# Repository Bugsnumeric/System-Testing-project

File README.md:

Diagrama proiectului:

Componente folosite impreuna cu detalii despre acestea:

| Component | Part Number | Package | Function | Datasheet |
|-----------|------------|---------|----------|-----------|
| MCU | nRF52840-QIAA-R | aQFN73 (7x7) | Microcontroller + BLE + USB | [Datasheet](https://docs.nordicsemi.com/) |
| Charger / Power Path | BQ25180YBGR | DSBGA-8 | Li-Ion/LiPo charger with power path | [Datasheet](https://www.ti.com/lit/ds/symlink/bq25180.pdf) |
| Buck-Boost Regulator | RT6160AWSC | WLCSP-15 | 3.3V system rail regulator | [Datasheet](https://www.richtek.com/assets/product_file/RT6160A/DS6160A-05.pdf) |
| Fuel Gauge | MAX17048G+T10 | DFN-8 (2x2) | Battery SOC monitoring | [Datasheet](https://www.analog.com/media/en/technical-documentation/data-sheets/MAX17048-MAX17049.pdf) |
| Accelerometer | BMA421 | LGA-12 (2x2) | Step counting + motion wake | [Datasheet](https://jlcpcb.com/partdetail/Bosch_Sensortec-BMA421/C5242966) |
| Haptic Driver | DRV2605LDGSR | VSSOP-10 | ERM motor driver with effects library | [Datasheet](https://www.ti.com/lit/ds/symlink/drv2605l.pdf) |
| PFET (EPD power) | SI2301CDS | SOT-23 | E-paper display power gating | [Datasheet](https://jlcpcb.com/partdetail/Changjiang_Electronics_Tech_CJ-SI2301CDS/C10487) |
| USB ESD Protection | USBLC6-2SC6Y | SOT-23-6 | ESD protection on USB data lines | [Datasheet](https://www.st.com/resource/en/datasheet/usblc6-2.pdf) |
| USB Type-C Connector | KH-TYPE-C-16P | 16-pin SMD | USB charging + data | [Datasheet](#) |

Descriere funcționalitate hardware

Interfețe:

I2C: încărcător LiPo, regulator DC/DC, IMU, fuel gauge, driver haptic
SPI: display e-paper

Sheet 1:

Încărcătorul LiPo gestionează încărcarea bateriei
Regulatorul DC/DC asigură o tensiune stabilă de 3.3V pentru sistem
IMU (accelerometru) măsoară accelerația pe 3 axe și permite funcții precum numărarea pașilor
Microcontrollerul nRF52840 coordonează toate funcțiile plăcii
Interfața SWD este utilizată pentru programare și debug

Sheet 2:

Circuitul de comandă pentru e-paper alimentează și controlează display-ul
Conectorul e-paper realizează legătura fizică cu display-ul
Fuel gauge monitorizează nivelul de încărcare al bateriei
Conectorul USB-C permite alimentarea și transferul de date
Protecția ESD previne deteriorarea cauzată de descărcări electrostatice
Driverul haptic controlează motorul de vibrație
Butoanele oferă interfața de control pentru utilizator

## Descriere pini nRF52840  

| Pin | Descriere |
|-----|----------|
| VDD | Alimentare 3V3 |
| DCC | Power regulation |
| DEC4 | Power regulation |
| VSS | GND |
| P0.31 / AIN7-4 | Nefolosit |
| P0.02 / AIN0 | SPI SCK (clock pentru display) |
| P0.02 / AIN0 | SPI MOSI (master output slave in) |
| P1.15–P1.12 | Nefolosit |
| DEC2 | GND, power regulation |
| P1.12–P1.11 | Nefolosit |
| VDD | Alimentare 3V3 |
| XC2, XC1 | Oscilator X1 (32 MHz) |
| DEC3 | GND |
| DEC6 | Power regulation |
| VSS_PA | Alimentare antenă |
| ANT | Conectare antenă |
| P0.10 / NFC2 | Semnal alertă baterie (Fuel Gauge) |
| P0.09 / NFC1 | Nefolosit |
| DEC5 | GND, power regulation |
| P1.07–P1.03 | Nefolosit |
| P1.02 | Buton Down |
| P1.01 | Control alimentare display |
| SWDIO, SWDCLK | Programare și debug |
| VDD | Alimentare 3V3 |
| VSS_PAD | GND |
| P1.00 | SWO (debug) |
| P0.25–P0.19 | Nefolosit |
| P0.18 / RESET | Pin Reset |
| P0.17, P0.16, P0.15 | Interfață display |
| P0.13, P0.14 | Butoane Enter / Up |
| D-, D+ | USB (transmisie diferențială) |
| VBUS | Alimentare USB 5V |
| DEC3V3 | GND (intern, power regulation) |
| DCCH | Nefolosit |
| VDDH, VDD | Alimentare 3V3 |
| P0.12 | Enable driver haptic |
| P0.11 | Alertă alimentare (de la LiPo Charger) |
| P1.09 | Nefolosit |
| P1.08, P0.08 | Interrupții IMU |
| P0.07, P0.06 | I2C (SCL, SDA) |
| P0.05 / AIN3 | Chip Select display |
| P0.04 / AIN2, P0.27, P0.26 | Nefolosit |
| XL2, XL1 | Oscilator X2 (32 kHz) |
| DEC1 | GND, power regulation |

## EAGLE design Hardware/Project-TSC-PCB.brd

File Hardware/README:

Print-out schematic:

https://a360.co/4sF2GDH

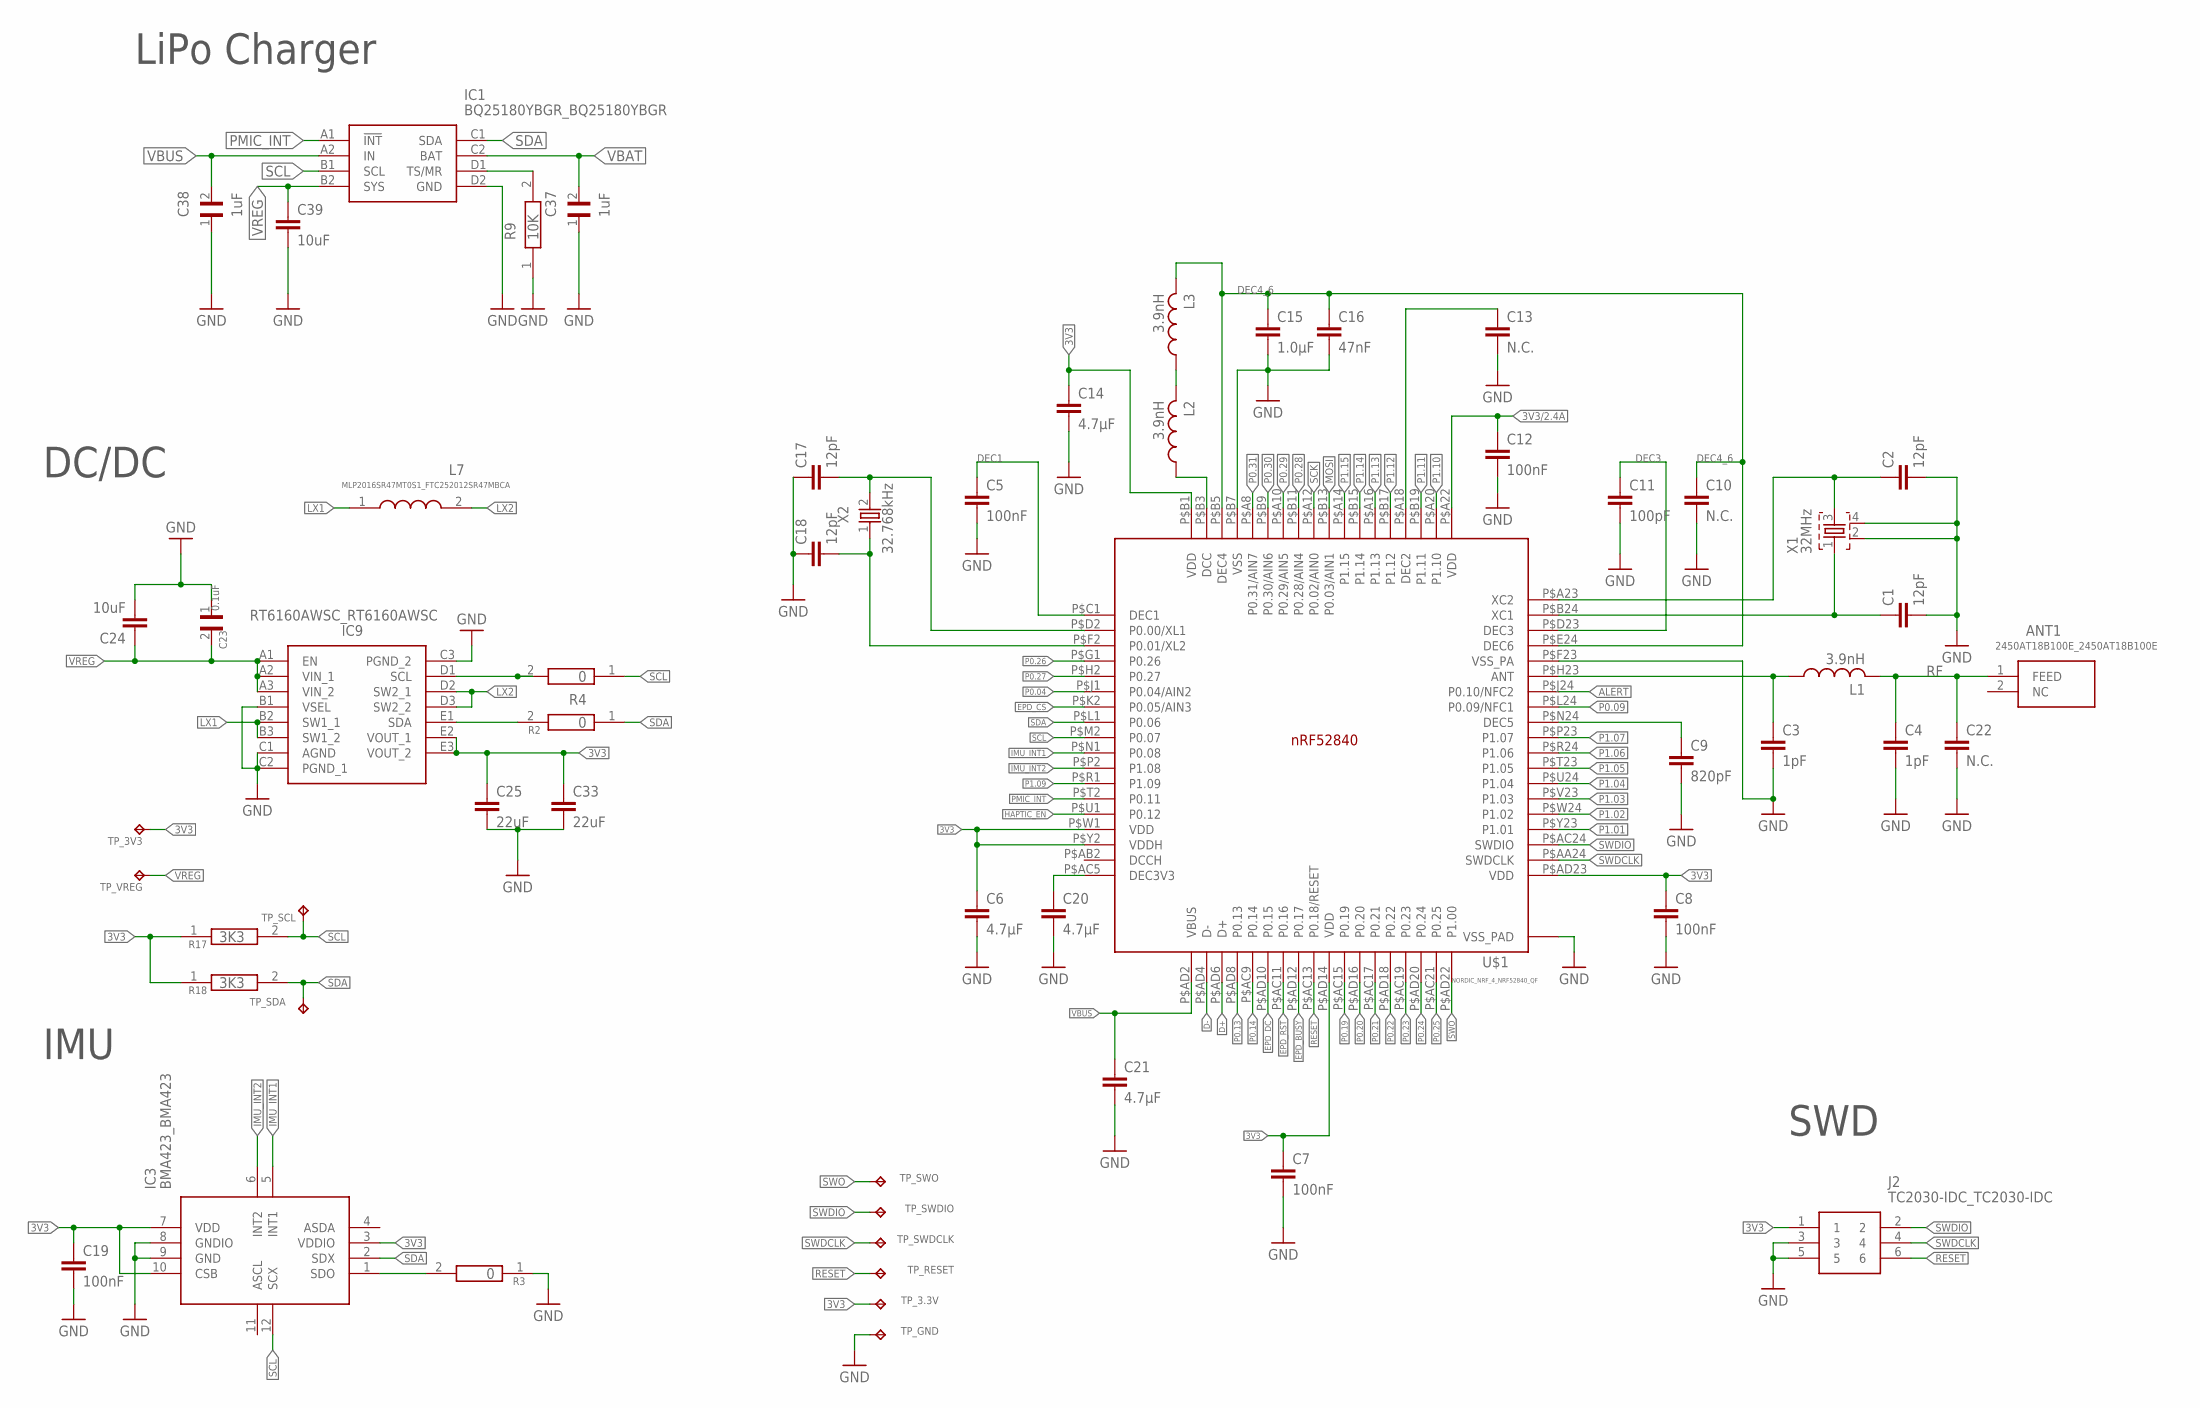
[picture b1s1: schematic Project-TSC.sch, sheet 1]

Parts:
ANT1: 2450AT18B100E_2450AT18B100E; 2450AT18B100E_ANTC3216X140N
C1, C2, C17, C18: 12pF; NORDIC_NRF_3_RESC0201_L
C3, C4: 1pF; NORDIC_NRF_3_RESC0201_L
C5, C7, C8, C12: 100nF; NORDIC_NRF_3_RESC0201_L
C6, C14, C20, C21: 4.7µF; PERFECT_0402_0402
C9: 820pF; NORDIC_NRF_3_RESC0201_L
C10, C13, C22: N.C.; NORDIC_NRF_3_RESC0201_L
C11: 100pF; NORDIC_NRF_3_RESC0201_L
C15: 1.0µF; PERFECT_0402_0402
C16: 47nF; NORDIC_NRF_3_RESC0201_L
C19: 100nF; PERFECT_0402_0402
C23: 0.1uF; GRM011R60J152KE01L_1_0201
C24, C39: 10uF; PERFECT_0402_0402
C25, C33: 22uF; PERFECT_0402_0402
C37, C38: 1uF; GRM011R60J152KE01L_1_0201
IC1: BQ25180YBGR_BQ25180YBGR; BQ25180YBGR_BGA8C40P2X4_100X155X50
IC3: BMA423_BMA423
IC9: RT6160AWSC_RT6160AWSC; RT6160AWSC_BGA15C40P3X5_140X230X60
J2: TC2030-IDC_TC2030-IDC; TC2030-IDC_TC2030IDC
L1, L2, L3: 3.9nH; NORDIC_NRF_2_RESC0402_L
L7: MLP2016SR47MT0S1_FTC252012SR47MBCA; MLP2016SR47MT0S1_INDC2016X100N
R2, R3, R4: 0; CPF0201D7K68C1_0201
R9: 10K; CPF0201D7K68C1_0201
R17, R18: 3K3; CPF0201D7K68C1_0201
TP_3.3V, TP_3V3: HECTOR_WATCH_1_TPTP20R; HECTOR_WATCH_1_TP20R
TP_GND: HECTOR_WATCH_1_TPTP20R; HECTOR_WATCH_1_TP20R
TP_RESET: HECTOR_WATCH_1_TPTP20R; HECTOR_WATCH_1_TP20R
TP_SCL: HECTOR_WATCH_1_TPTP20R; HECTOR_WATCH_1_TP20R
TP_SDA: HECTOR_WATCH_1_TPTP20R; HECTOR_WATCH_1_TP20R
TP_SWDCLK: HECTOR_WATCH_1_TPTP20R; HECTOR_WATCH_1_TP20R
TP_SWDIO: HECTOR_WATCH_1_TPTP20R; HECTOR_WATCH_1_TP20R
TP_SWO: HECTOR_WATCH_1_TPTP20R; HECTOR_WATCH_1_TP20R
TP_VREG: HECTOR_WATCH_1_TPTP20R; HECTOR_WATCH_1_TP20R
U$1: NORDIC_NRF_4_NRF52840_QF; NORDIC_NRF_4_AQFN50P700X700X85_HS-74N
X1: 32MHz; NORDIC_NRF_BT-XTAL_2016_N
X2: 32.768kHz; NORDIC_NRF_1_XTAL_3215_N

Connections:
3V3: C6.1, C7.1, C8.1, C14.1, C19.1, C25.1, C33.1, IC3.3 (VDDIO), IC3.7 (VDD), IC3.10 (CSB), IC9.E2 (VOUT_1), IC9.E3 (VOUT_2), J2.1, R17.1, R18.1, TP_3.3V.TP, TP_3V3.TP, U$1.P$AD14 (VDD), U$1.P$AD23 (VDD), U$1.P$B1 (VDD), U$1.P$W1 (VDD), U$1.P$Y2 (VDDH); also elsewhere on the board
3V3/2.4A: C12.1, U$1.P$A22 (VDD)
ALERT: U$1.P$J24 (P0.10/NFC2); also elsewhere on the board
D+: U$1.P$AD6 (D+); also elsewhere on the board
D-: U$1.P$AD4 (D-); also elsewhere on the board
DEC1: C5.1, U$1.P$C1 (DEC1)
DEC3: C11.1, U$1.P$D23 (DEC3)
DEC4_6: C10.1, C15.1, C16.1, L3.2, U$1.P$B5 (DEC4), U$1.P$E24 (DEC6)
EPD_BUSY: U$1.P$AD12 (P0.17); also elsewhere on the board
EPD_CS: U$1.P$K2 (P0.05/AIN3); also elsewhere on the board
EPD_DC: U$1.P$AD10 (P0.15); also elsewhere on the board
EPD_RST: U$1.P$AC11 (P0.16); also elsewhere on the board
GND: C1.2, C2.2, C3.2, C4.2, C5.2, C6.2, C7.2, C8.2, C9.2, C10.2, C11.2, C12.2, C13.2, C14.2, C15.2, C16.2, C17.1, C18.1, C19.2, C20.2, C21.2, C22.2, C23.1, C24.2, C25.2, C33.2, C37.1, C38.1, C39.2, IC1.D2 (GND), IC3.8 (GNDIO), IC3.9 (GND), IC9.B1 (VSEL), IC9.C1 (AGND), IC9.C2 (PGND_1), IC9.C3 (PGND_2), J2.3, J2.5, R3.1, R9.1, TP_GND.TP, U$1.P$74 (VSS_PAD), U$1.P$75 (VSS_PAD), U$1.P$76 (VSS_PAD), U$1.P$77 (VSS_PAD), U$1.P$78 (VSS_PAD), U$1.P$79 (VSS_PAD), U$1.P$80 (VSS_PAD), U$1.P$81 (VSS_PAD), U$1.P$82 (VSS_PAD), U$1.P$83 (VSS_PAD), U$1.P$84 (VSS_PAD), U$1.P$85 (VSS_PAD), U$1.P$86 (VSS_PAD), U$1.P$87 (VSS_PAD), U$1.P$88 (VSS_PAD), U$1.P$89 (VSS_PAD), U$1.P$90 (VSS_PAD), U$1.P$B7 (VSS), U$1.P$F23 (VSS_PA), X1.2, X1.4; also elsewhere on the board
HAPTIC_EN: U$1.P$U1 (P0.12); also elsewhere on the board
IMU_INT1: IC3.5 (INT1), U$1.P$N1 (P0.08)
IMU_INT2: IC3.6 (INT2), U$1.P$P2 (P1.08)
LX1: IC9.B2 (SW1_1), IC9.B3 (SW1_2), L7.1
LX2: IC9.D2 (SW2_1), IC9.D3 (SW2_2), L7.2
MOSI: U$1.P$B13 (P0.03/AIN1); also elsewhere on the board
unnamed: IC1.D1 (TS/MR), R9.2
unnamed: C9.1, U$1.P$N24 (DEC5)
unnamed: IC9.D1 (SCL), R4.2
unnamed: IC9.E1 (SDA), R2.2
unnamed: IC3.1 (SDO), R3.2
unnamed: C3.1, L1.1, U$1.P$H23 (ANT)
unnamed: C1.1, U$1.P$B24 (XC1), X1.1
unnamed: C2.1, U$1.P$A23 (XC2), X1.3
unnamed: C13.1, U$1.P$A18 (DEC2)
unnamed: L2.2, L3.1
unnamed: L2.1, U$1.P$B3 (DCC)
unnamed: C17.2, U$1.P$D2 (P0.00/XL1), X2.2
unnamed: C18.2, U$1.P$F2 (P0.01/XL2), X2.1
unnamed: C20.1, U$1.P$AC5 (DEC3V3)
P0.04: U$1.P$J1 (P0.04/AIN2)
P0.09: U$1.P$L24 (P0.09/NFC1)
P0.13: U$1.P$AD8 (P0.13); also elsewhere on the board
P0.14: U$1.P$AC9 (P0.14); also elsewhere on the board
P0.19: U$1.P$AC15 (P0.19)
P0.20: U$1.P$AD16 (P0.20)
P0.21: U$1.P$AC17 (P0.21)
P0.22: U$1.P$AD18 (P0.22)
P0.23: U$1.P$AC19 (P0.23)
P0.24: U$1.P$AD20 (P0.24)
P0.25: U$1.P$AC21 (P0.25)
P0.26: U$1.P$G1 (P0.26)
P0.27: U$1.P$H2 (P0.27)
P0.28: U$1.P$B11 (P0.28/AIN4)
P0.29: U$1.P$A10 (P0.29/AIN5)
P0.30: U$1.P$B9 (P0.30/AIN6)
P0.31: U$1.P$A8 (P0.31/AIN7)
P1.01: U$1.P$Y23 (P1.01); also elsewhere on the board
P1.02: U$1.P$W24 (P1.02); also elsewhere on the board
P1.03: U$1.P$V23 (P1.03)
P1.04: U$1.P$U24 (P1.04)
P1.05: U$1.P$T23 (P1.05)
P1.06: U$1.P$R24 (P1.06)
P1.07: U$1.P$P23 (P1.07)
P1.09: U$1.P$R1 (P1.09)
P1.10: U$1.P$A20 (P1.10)
P1.11: U$1.P$B19 (P1.11)
P1.12: U$1.P$B17 (P1.12)
P1.13: U$1.P$A16 (P1.13)
P1.14: U$1.P$B15 (P1.14)
P1.15: U$1.P$A14 (P1.15)
PMIC_INT: IC1.A1 (!INT), U$1.P$T2 (P0.11)
RESET: J2.6, TP_RESET.TP, U$1.P$AC13 (P0.18/RESET)
RF: ANT1.1 (FEED), C4.1, C22.1, L1.2
SCK: U$1.P$A12 (P0.02/AIN0); also elsewhere on the board
SCL: IC1.B1 (SCL), IC3.12 (SCX), R4.1, R17.2, TP_SCL.TP, U$1.P$M2 (P0.07); also elsewhere on the board
SDA: IC1.C1 (SDA), IC3.2 (SDX), R2.1, R18.2, TP_SDA.TP, U$1.P$L1 (P0.06); also elsewhere on the board
SWDCLK: J2.4, TP_SWDCLK.TP, U$1.P$AA24 (SWDCLK)
SWDIO: J2.2, TP_SWDIO.TP, U$1.P$AC24 (SWDIO)
SWO: TP_SWO.TP, U$1.P$AD22 (P1.00)
VBAT: C37.2, IC1.C2 (BAT); also elsewhere on the board
VBUS: C21.1, C38.2, IC1.A2 (IN), U$1.P$AD2 (VBUS); also elsewhere on the board
VREG: C23.2, C24.1, C39.1, IC1.B2 (SYS), IC9.A1 (EN), IC9.A2 (VIN_1), IC9.A3 (VIN_2), TP_VREG.TP

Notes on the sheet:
LiPo Charger
DC/DC
IMU
SWD

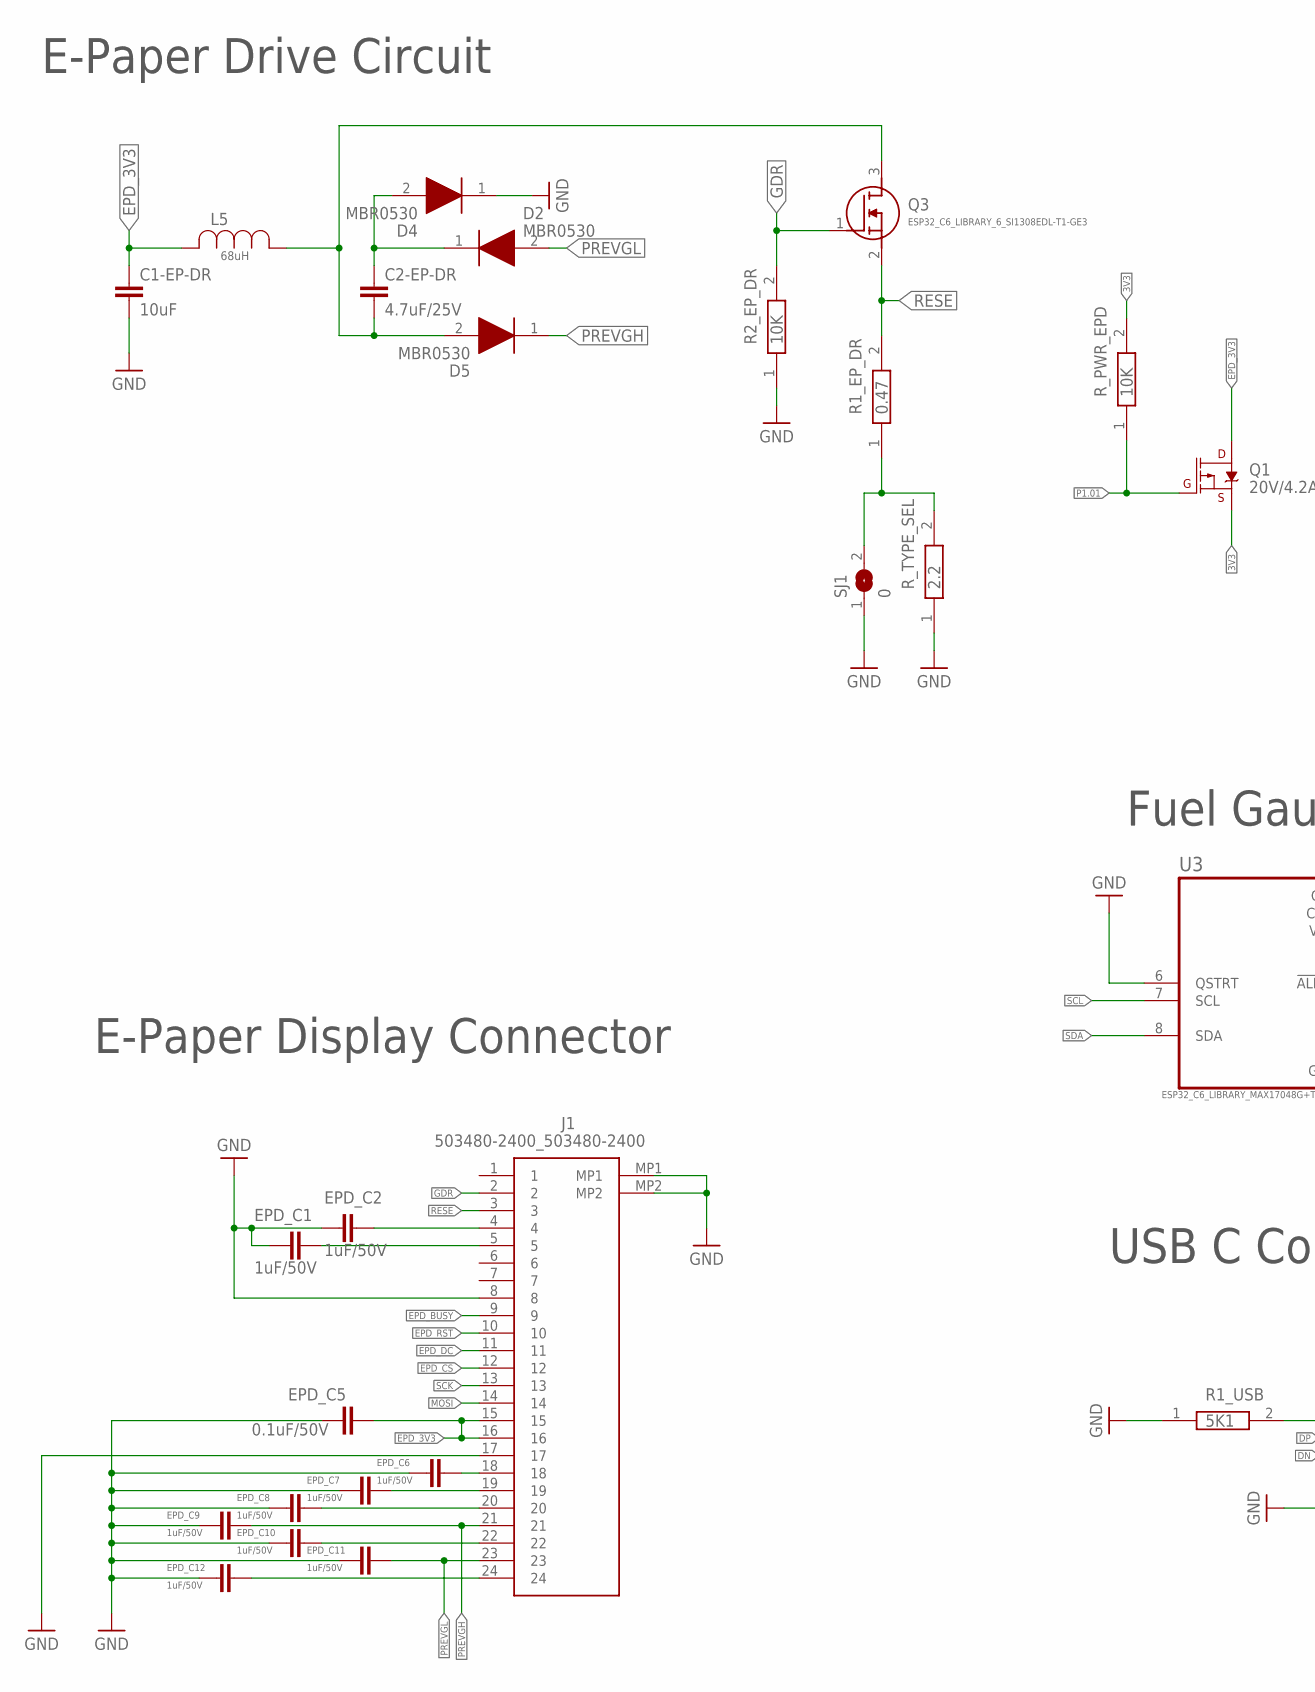
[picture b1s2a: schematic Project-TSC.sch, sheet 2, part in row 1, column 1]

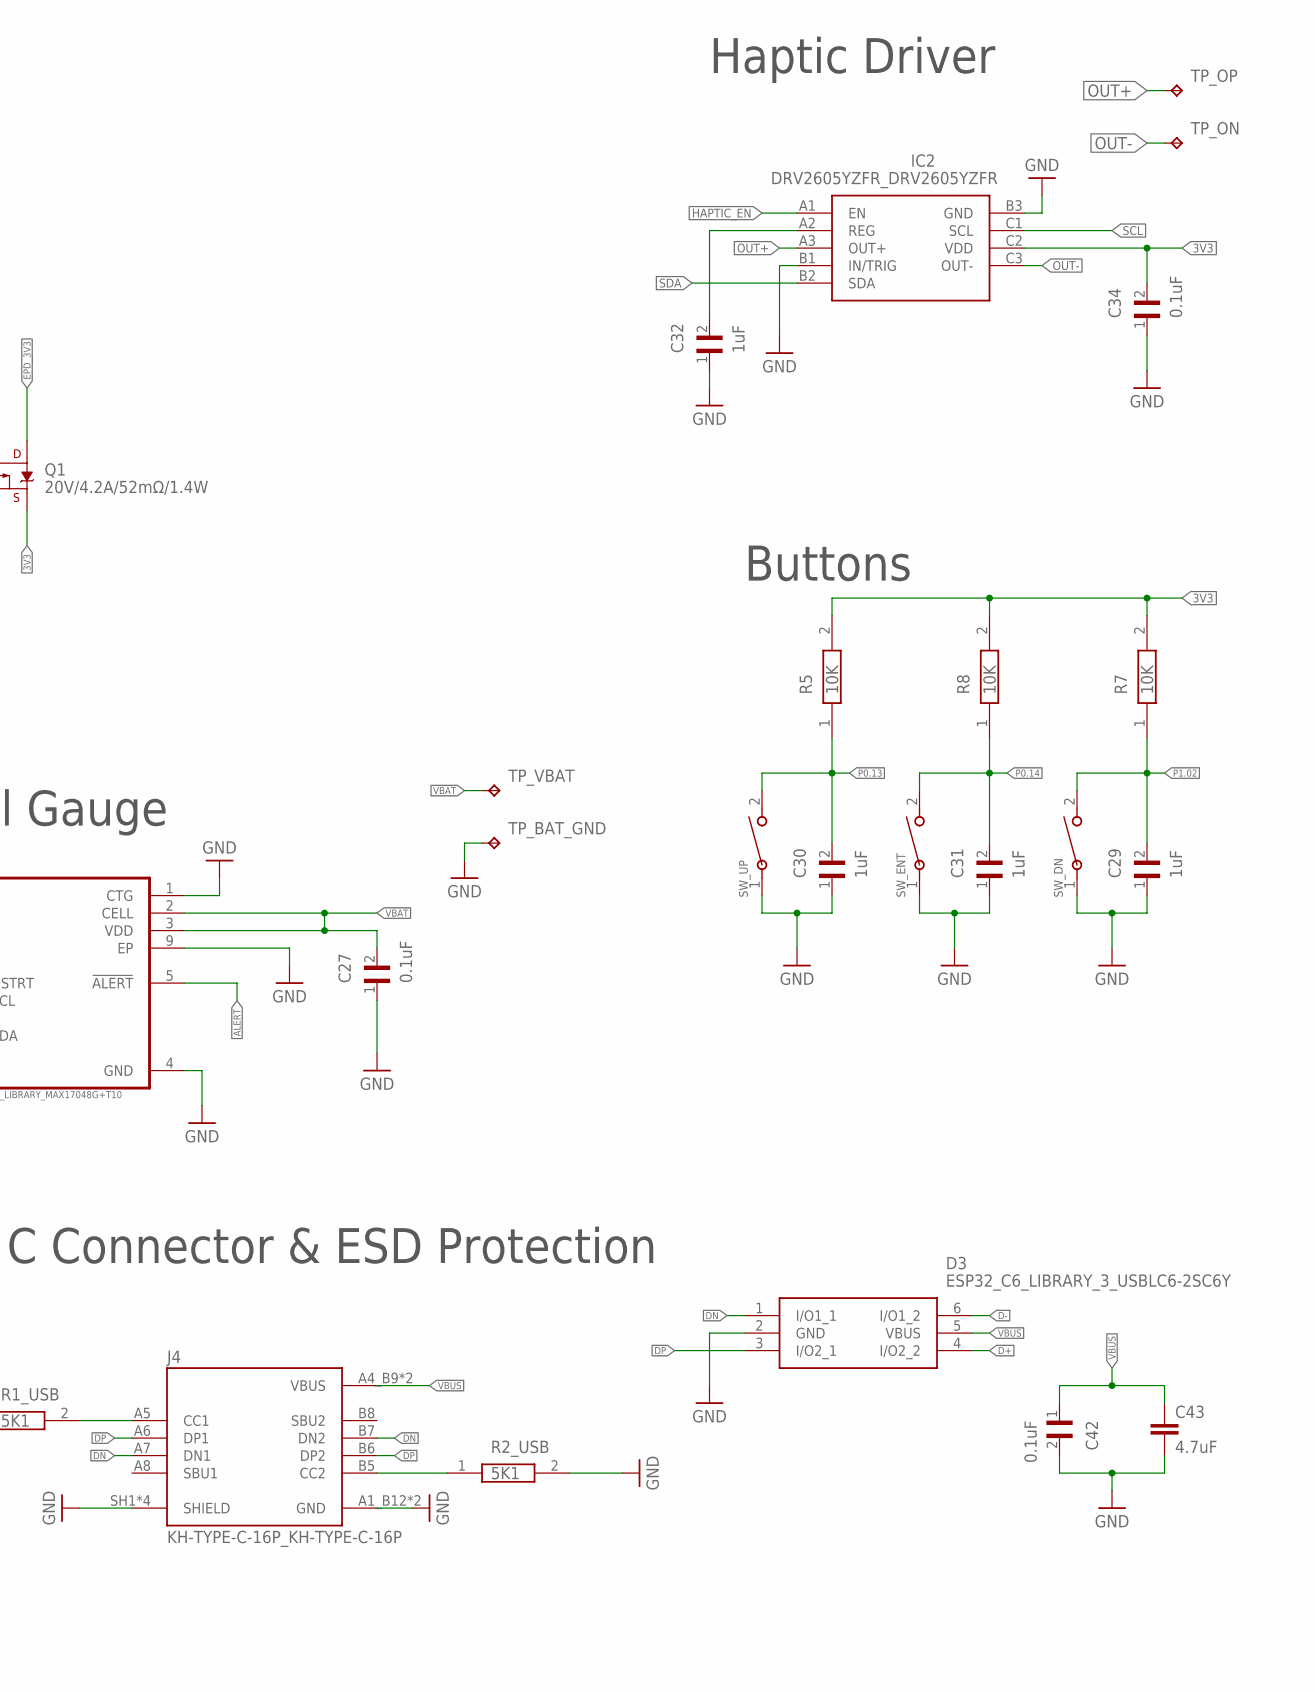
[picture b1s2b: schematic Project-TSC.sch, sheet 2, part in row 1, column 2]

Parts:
C1-EP-DR: 10uF; PERFECT_0402_0402
C2-EP-DR: 4.7uF/25V; PERFECT_0402_0402
C27, C34, C42: 0.1uF; GRM011R60J152KE01L_2_CAPC0201X13N
C29, C30, C31, C32: 1uF; GRM011R60J152KE01L_2_CAPC0201X13N
C43: 4.7uF; PERFECT_0402_0402
D2, D4, D5: MBR0530; ESP32_C6_LIBRARY_5_SOD3716X135N
D3: ESP32_C6_LIBRARY_3_USBLC6-2SC6Y; ESP32_C6_LIBRARY_3_SOT95P280X145-6N
EPD_C1, EPD_C2, EPD_C6, EPD_C7, EPD_C8, EPD_C9, EPD_C10, EPD_C11, EPD_C12: 1uF/50V; PERFECT_0402_0402
EPD_C5: 0.1uF/50V; NORDIC_NRF_3_RESC0201_L
IC2: DRV2605YZFR_DRV2605YZFR; DRV2605YZFR_BGA9C50P3X3_144X144X62
J1: 503480-2400_503480-2400; 503480-2400_5034802400
J4: KH-TYPE-C-16P_KH-TYPE-C-16P; KH-TYPE-C-16P_KINGHELM_KH-TYPE-C-16P
L5: 68uH; ESP32_C6_LIBRARY_2_IND_4828-WE-TPC_WRE
Q1: 20V/4.2A/52mΩ/1.4W; ESP32_C6_LIBRARY_4_ESP32_C6_LIBRARY_4_ESP32_C6_LIBRARY_4_ES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
Q3: ESP32_C6_LIBRARY_6_SI1308EDL-T1-GE3; ESP32_C6_LIBRARY_6_SOT65P210X110-3N
R1_EP_DR: 0.47; CPF0201D7K68C1_0201
R1_USB, R2_USB: 5K1; CPF0201D7K68C1_0201
R2_EP_DR, R5, R7, R8: 10K; CPF0201D7K68C1_0201
R_PWR_EPD: 10K; CPF0201D7K68C1_0201
R_TYPE_SEL: 2.2; CPF0201D7K68C1_0201
SJ1: 0; ESP32_C6_LIBRARY_7_JUMPER_SJ
SW_DN: 2025-10-22_07-23-44_LIBRARY_EVP-AKE31ASW_EVP-AKE3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; 2025-10-22_07-23-44_LIBRARY_SW_EVP-AKE31A_PAN
SW_ENT: 2025-10-22_07-23-44_LIBRARY_EVP-AKE31ASW_EVP-AKE3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; 2025-10-22_07-23-44_LIBRARY_SW_EVP-AKE31A_PAN
SW_UP: 2025-10-22_07-23-44_LIBRARY_EVP-AKE31ASW_EVP-AKE3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; 2025-10-22_07-23-44_LIBRARY_SW_EVP-AKE31A_PAN
TP_BAT_GND: HECTOR_WATCH_1_TPTP20R; HECTOR_WATCH_1_TP20R
TP_ON: HECTOR_WATCH_1_TPTP20R; HECTOR_WATCH_1_TP20R
TP_OP: HECTOR_WATCH_1_TPTP20R; HECTOR_WATCH_1_TP20R
TP_VBAT: HECTOR_WATCH_1_TPTP20R; HECTOR_WATCH_1_TP20R
U3: ESP32_C6_LIBRARY_MAX17048G+T10; ESP32_C6_LIBRARY_SON50P200X200X80-9N

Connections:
3V3: C34.2, IC2.C2 (VDD), Q1.2 (S), R5.2, R7.2, R8.2, R_PWR_EPD.2; also elsewhere on the board
ALERT: U3.5 (!ALERT); also elsewhere on the board
D+: D3.4 (I/O2_2); also elsewhere on the board
D-: D3.6 (I/O1_2); also elsewhere on the board
DN: D3.1 (I/O1_1), J4.A7 (DN1), J4.B7 (DN2)
DP: D3.3 (I/O2_1), J4.A6 (DP1), J4.B6 (DP2)
EPD_3V3: C1-EP-DR.1, EPD_C5.2, J1.15, J1.16, L5.2, Q1.3 (D)
EPD_BUSY: J1.9; also elsewhere on the board
EPD_CS: J1.12; also elsewhere on the board
EPD_DC: J1.11; also elsewhere on the board
EPD_RST: J1.10; also elsewhere on the board
GDR: J1.2, Q3.1 (G), R2_EP_DR.2
GND: C1-EP-DR.2, C27.1, C29.1, C30.1, C31.1, C32.1, C34.1, C42.2, C43.2, D3.2 (GND), D4.1 (K), EPD_C1.2, EPD_C2.2, EPD_C5.1, EPD_C6.2, EPD_C7.2, EPD_C8.2, EPD_C9.2, EPD_C10.2, EPD_C11.2, EPD_C12.2, IC2.B1 (IN/TRIG), IC2.B3 (GND), J1.8, J1.17, J1.MP1, J1.MP2, J4.A1_B12 (GND), J4.A12_B1 (GND), J4.SH1 (SHIELD), J4.SH2 (SHIELD), J4.SH3 (SHIELD), J4.SH4 (SHIELD), R1_USB.1, R2_EP_DR.1, R2_USB.2, R_TYPE_SEL.1, SJ1.1, SW_DN.1, SW_ENT.1, SW_UP.1, TP_BAT_GND.TP, U3.1 (CTG), U3.4 (GND), U3.6 (QSTRT), U3.9 (EP); also elsewhere on the board
HAPTIC_EN: IC2.A1 (EN); also elsewhere on the board
MOSI: J1.14; also elsewhere on the board
unnamed: C2-EP-DR.1, D2.1 (K), D4.2 (A)
unnamed: C2-EP-DR.2, D5.2 (A), L5.1, Q3.3 (D)
unnamed: J4.A5 (CC1), R1_USB.2
unnamed: J4.B5 (CC2), R2_USB.1
unnamed: EPD_C2.1, J1.4
unnamed: R1_EP_DR.1, R_TYPE_SEL.2, SJ1.2
unnamed: C32.2, IC2.A2 (REG)
unnamed: EPD_C1.1, J1.5
unnamed: EPD_C6.1, J1.18
unnamed: EPD_C7.1, J1.19
unnamed: EPD_C8.1, J1.20
unnamed: EPD_C10.1, J1.22
unnamed: EPD_C12.1, J1.24
OUT+: IC2.A3 (OUT+), TP_OP.TP
OUT-: IC2.C3 (OUT-), TP_ON.TP
P0.13: C30.2, R5.1, SW_UP.2; also elsewhere on the board
P0.14: C31.2, R8.1, SW_ENT.2; also elsewhere on the board
P1.01: Q1.1 (G), R_PWR_EPD.1; also elsewhere on the board
P1.02: C29.2, R7.1, SW_DN.2; also elsewhere on the board
PREVGH: D5.1 (K), EPD_C9.1, J1.21
PREVGL: D2.2 (A), EPD_C11.1, J1.23
RESE: J1.3, Q3.2 (S), R1_EP_DR.2
SCK: J1.13; also elsewhere on the board
SCL: IC2.C1 (SCL), U3.7 (SCL); also elsewhere on the board
SDA: IC2.B2 (SDA), U3.8 (SDA); also elsewhere on the board
VBAT: C27.2, TP_VBAT.TP, U3.2 (CELL), U3.3 (VDD); also elsewhere on the board
VBUS: C42.1, C43.1, D3.5 (VBUS), J4.A4_B9 (VBUS), J4.A9_B4 (VBUS); also elsewhere on the board

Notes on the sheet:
E-Paper Drive Circuit
Haptic Driver
Buttons
Fuel Gauge
USB C Connector & ESD Protection
E-Paper Display Connector

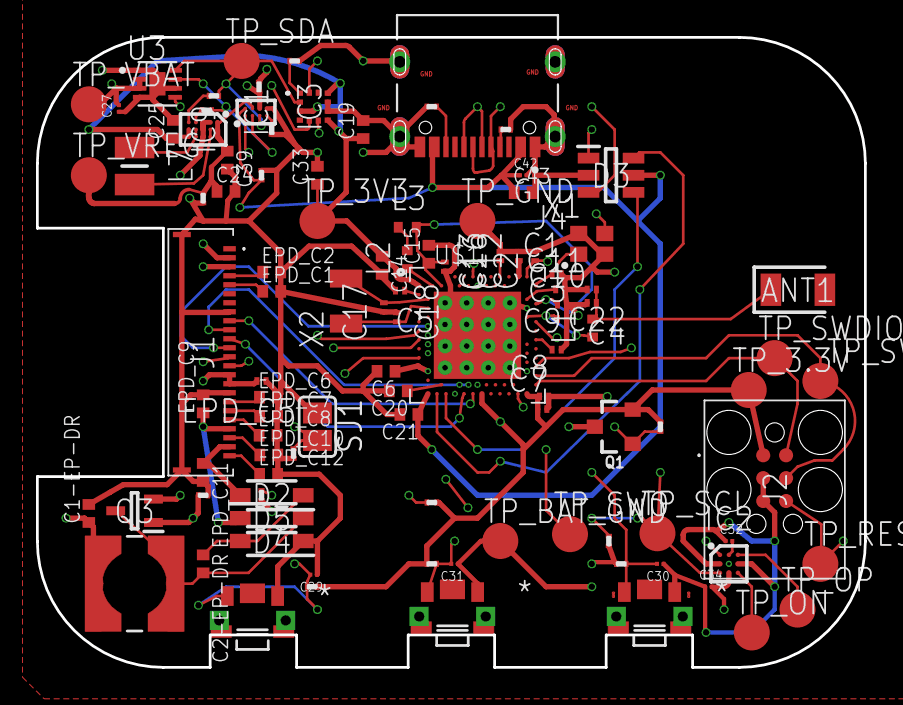
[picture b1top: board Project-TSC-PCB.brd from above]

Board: 4 copper layers, 46.0 x 35.0 mm, 105 parts (0 on the bottom side), 71 nets.

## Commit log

2026-04-10 LICENSE
2026-04-19 Project-ST
2026-04-19 Diagram
2026-04-19 README
2026-04-19 Images
2026-04-20 Hardware

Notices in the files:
parts and their libraries:
COPYRIGHT: Copyright (C) 2024 Ultra Librarian. All rights reserved.
COPYRIGHT: Copyright (C) 2025 Ultra Librarian. All rights reserved.
